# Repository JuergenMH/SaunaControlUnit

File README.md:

# SaunaControlUnit
Control unit for sauna oven. Ensures comfort and safety.
Cheap control units are good for regualation and some basic safetey functions.
This project is designed to add some comfort and safety topics
- Enhanced safety by control internal power lines and oven function
- Enhanced comfort: Acceess via WLAN
- Two relay banks to ensure the system in case of one relay fails

Folders:
Components: Datasheets and information hardware component related
Documents:  Planning Documents
SaunaPCB:   KiCAD folder for schematic and PCB design files
Simulation: Folder for LTSpice simulation fils
Firmware:   Planned for firmware files, currently empty

Sorry, some documents are available in German only ;-)

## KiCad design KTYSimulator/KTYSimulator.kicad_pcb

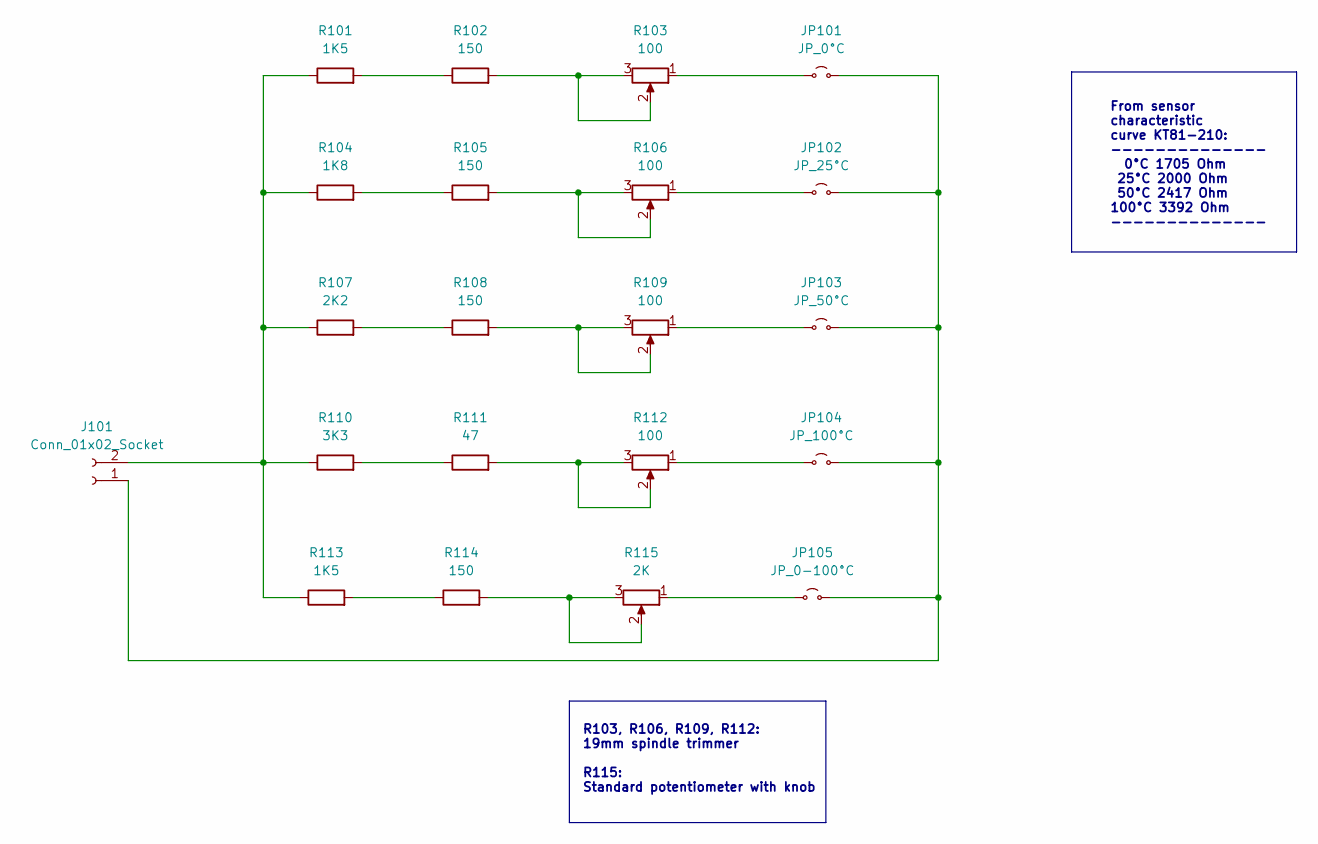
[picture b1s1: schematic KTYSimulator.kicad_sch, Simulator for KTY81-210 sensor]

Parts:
J101: Conn_01x02_Socket; PinHeader_1x02_P2.54mm_Vertical
JP101: JP_0°C; PinHeader_1x02_P2.54mm_Vertical
JP102: JP_25°C; PinHeader_1x02_P2.54mm_Vertical
JP103: JP_50°C; PinHeader_1x02_P2.54mm_Vertical
JP104: JP_100°C; PinHeader_1x02_P2.54mm_Vertical
JP105: JP_0-100°C; PinHeader_1x02_P2.54mm_Vertical
R101, R113: 1K5; R_Axial_DIN0207_L6.3mm_D2.5mm_P10.16mm_Horizontal
R102, R105, R108, R114: 150; R_Axial_DIN0207_L6.3mm_D2.5mm_P10.16mm_Horizontal
R103, R106, R109, R112: 100; Potentiometer_Bourns_3005_Horizontal
R104: 1K8; R_Axial_DIN0207_L6.3mm_D2.5mm_P10.16mm_Horizontal
R107: 2K2; R_Axial_DIN0207_L6.3mm_D2.5mm_P10.16mm_Horizontal
R110: 3K3; R_Axial_DIN0207_L6.3mm_D2.5mm_P10.16mm_Horizontal
R111: 47; R_Axial_DIN0207_L6.3mm_D2.5mm_P10.16mm_Horizontal
R115: 2K; Potentiometer_Alps_RK09Y11_Single_Horizontal

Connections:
unnamed: J101.1, JP101.2 (B), JP102.2 (B), JP103.2 (B), JP104.2 (B), JP105.2 (B)
unnamed: J101.2, R101.1, R104.1, R107.1, R110.1, R113.1
unnamed: JP101.1 (A), R103.1
unnamed: JP102.1 (A), R106.1
unnamed: JP103.1 (A), R109.1
unnamed: JP104.1 (A), R112.1
unnamed: JP105.1 (A), R115.1
unnamed: R101.2, R102.1
unnamed: R102.2, R103.2, R103.3
unnamed: R104.2, R105.1
unnamed: R105.2, R106.2, R106.3
unnamed: R107.2, R108.1
unnamed: R108.2, R109.2, R109.3
unnamed: R110.2, R111.1
unnamed: R111.2, R112.2, R112.3
unnamed: R113.2, R114.1
unnamed: R114.2, R115.2, R115.3

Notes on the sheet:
From sensor characteristic curve KT81-210: -------------- 0°C 1705 Ohm 25°C 2000 Ohm 50°C 2417 Ohm 100°C 3392 Ohm --------------
R103, R106, R109, R112: 19mm spindle trimmer R115: Standard potentiometer with knob

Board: 2 copper layers, 21 parts (0 on the bottom side), 17 nets, no tracks yet.

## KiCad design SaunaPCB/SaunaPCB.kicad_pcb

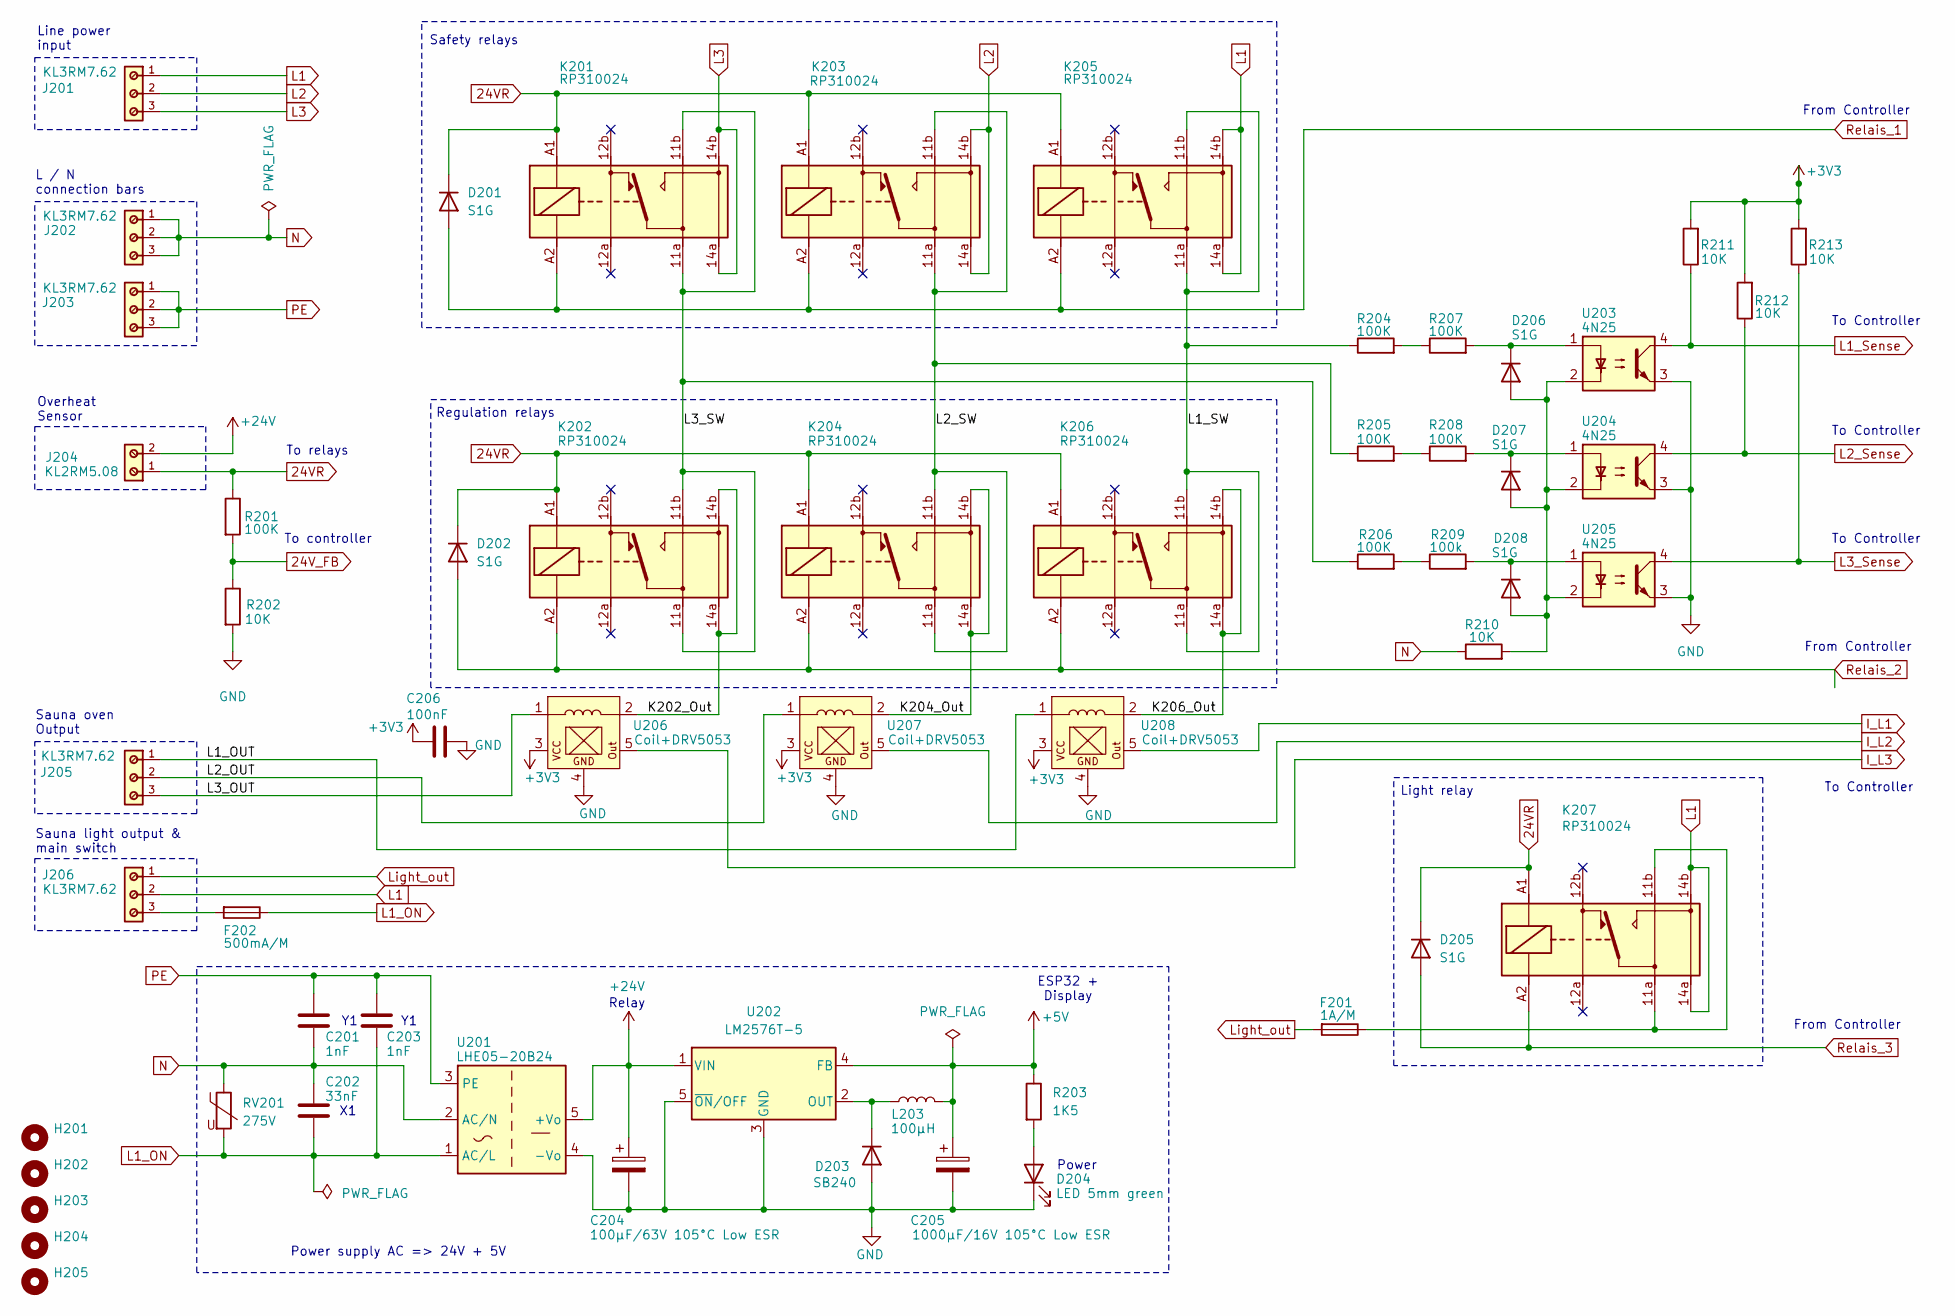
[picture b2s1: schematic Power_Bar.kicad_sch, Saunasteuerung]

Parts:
C201, C203: 1nF; C_Axial_L12.0mm_D6.5mm_P15.00mm_Horizontal
C202: 33nF; C_Axial_L12.0mm_D6.5mm_P15.00mm_Horizontal
C204: 100µF/63V 105°C Low ESR; CP_Radial_D10.0mm_P5.00mm
C205: 1000µF/16V 105°C Low ESR; CP_Radial_D10.0mm_P5.00mm
C206: 100nF; C_0805_2012Metric
D201, D202, D205, D206, D207, D208: S1G; D_SMA_Handsoldering
D203: SB240; D_A-405_P10.16mm_Horizontal
D204: LED 5mm green; B2B-ZR
F201: 1A/M; Fuseholder_Cylinder-5x20mm_Schurter_0031_8201_Horizontal_Op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
F202: 500mA/M; Fuseholder_Cylinder-5x20mm_Schurter_0031_8201_Horizontal_Op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
H201, H202, H203, H204, H205: MountingHole; MountingHole_3.2mm_M3_DIN965
J201, J202, J203, J205, J206: KL3RM7.62; Terminal_Block_3_RM7.62
J204: KL2RM5.08; Terminal_Block_2_RM5.08
K201, K202, K203, K204, K205, K206, K207: RP310024; Standard_Relay_double Pins
L203: 100µH; L_Radial_D7.5mm_P5.00mm_Fastron_07P
R201, R204, R205, R206, R207, R208: 100K; R_1206_3216Metric
R202, R210, R211, R212, R213: 10K; R_1206_3216Metric
R203: 1K5; R_1206_3216Metric
R209: 100k; R_1206_3216Metric
RV201: 275V; RV_Disc_D12mm_W4.2mm_P7.5mm
U201: LHE05-20B24
U202: LM2576T-5; TO-220-5_Vertical
U203, U204, U205: 4N25; DIP-4_W7.62mm
U206, U207, U208: Coil+DRV5053; Current_Coil_19X14_w_Hall

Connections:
24VR: D201.1 (K), D202.1 (K), D205.1 (K), J204.1, K201.A1, K202.A1, K203.A1, K204.A1, K205.A1, K206.A1, K207.A1, R201.1; also elsewhere on the board
24V_FB: R201.2, R202.1; also elsewhere on the board
+3V3: C206.1, R211.2, R212.2, R213.2, U206.3, U207.3, U208.3; also elsewhere on the board
+5V: C205.1, L203.2, R203.1, U202.4 (FB); also elsewhere on the board
+24V: C204.1, J204.2, U201.5 (+Vo), U202.1 (VIN)
/Power distribution part/K202_Out: K202.14a, K202.14b, U206.2
/Power distribution part/K204_Out: K204.14a, K204.14b, U207.2
/Power distribution part/K206_Out: K206.14a, K206.14b, U208.2
/Power distribution part/L1_OUT: J205.1, U208.1
/Power distribution part/L1_SW: K205.11a, K205.11b, K206.11a, K206.11b, R204.1
/Power distribution part/L2_OUT: J205.2, U207.1
/Power distribution part/L2_SW: K203.11a, K203.11b, K204.11a, K204.11b, R205.1
/Power distribution part/L3_OUT: J205.3, U206.1
/Power distribution part/L3_SW: K201.11a, K201.11b, K202.11a, K202.11b, R206.1
GND: C204.2, C205.2, C206.2, D203.2 (A), D204.1 (K), R202.2, U201.4 (-Vo), U202.3 (GND), U202.5 (~ON/OFF), U203.3, U204.3, U205.3, U206.4, U207.4, U208.4; also elsewhere on the board
I_L1: U208.5; also elsewhere on the board
I_L2: U207.5; also elsewhere on the board
I_L3: U206.5; also elsewhere on the board
L1: J201.1, J206.2, K205.14a, K205.14b, K207.14a, K207.14b
L1_ON: C202.2, C203.2, F202.1, RV201.2, U201.1 (AC/L)
L1_Sense: R211.1, U203.4; also elsewhere on the board
L2: J201.2, K203.14a, K203.14b
L2_Sense: R212.1, U204.4; also elsewhere on the board
L3: J201.3, K201.14a, K201.14b
L3_Sense: R213.1, U205.4; also elsewhere on the board
Light_out: F201.2, J206.1
N: C201.2, C202.1, J202.1, J202.2, J202.3, R210.1, RV201.1, U201.2 (AC/N)
unnamed: D203.1 (K), L203.1, U202.2 (OUT)
unnamed: D204.2 (A), R203.2
unnamed: D206.2 (A), D207.2 (A), D208.2 (A), R210.2, U203.2, U204.2, U205.2
unnamed: D206.1 (K), R207.2, U203.1
unnamed: D207.1 (K), R208.2, U204.1
unnamed: D208.1 (K), R209.2, U205.1
unnamed: F201.1, K207.11a, K207.11b
unnamed: F202.2, J206.3
unnamed: R204.2, R207.1
unnamed: R205.2, R208.1
unnamed: R206.2, R209.1
PE: C201.1, C203.1, J203.1, J203.2, J203.3, U201.3 (PE)
Relais_1: D201.2 (A), K201.A2, K203.A2, K205.A2; also elsewhere on the board
Relais_2: D202.2 (A), K202.A2, K204.A2, K206.A2; also elsewhere on the board
Relais_3: D205.2 (A), K207.A2; also elsewhere on the board

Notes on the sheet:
From Controller
Power supply AC => 24V + 5V
Regulation relays
L / N connection bars
To Controller
Light relay
Overheat Sensor
Sauna oven Output
To relays
To controller
Safety relays
Line power input
Sauna light output & main switch
Power
ESP32 + Display
Relay

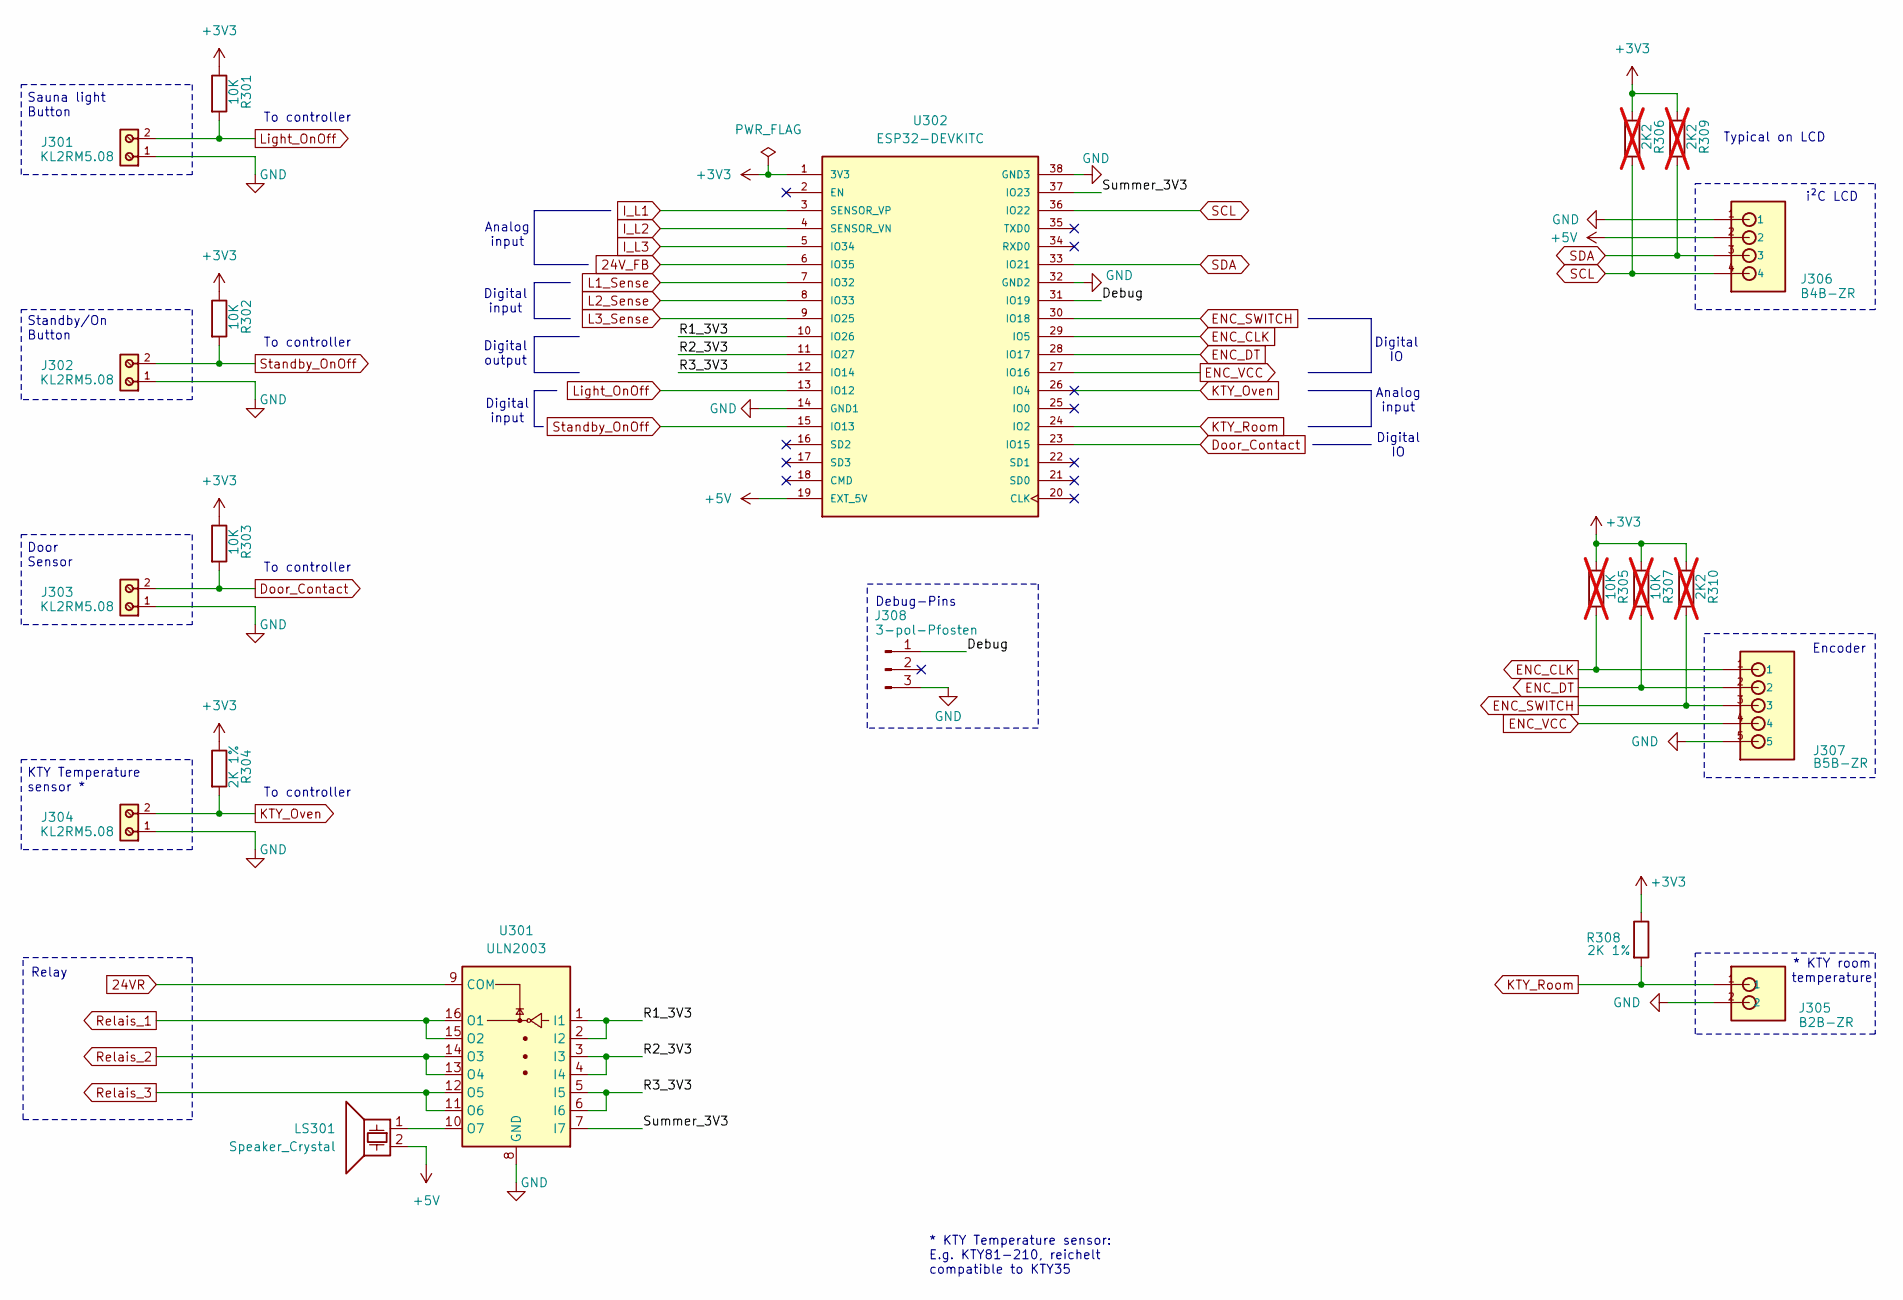
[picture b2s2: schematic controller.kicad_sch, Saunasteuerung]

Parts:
J301, J302, J303, J304: KL2RM5.08; Terminal_Block_2_RM5.08
J305: B2B-ZR
J306: B4B-ZR
J307: B5B-ZR
J308: 3-pol-Pfosten; PinHeader_1x03_P1.00mm_Vertical
LS301: Speaker_Crystal; Buzzer_TDK_PS1240P02BT_D12.2mm_H6.5mm
R301, R302, R303: 10K; R_1206_3216Metric
R304, R308: 2K 1%; R_1206_3216Metric
R305, R307: 10K; R_1206_3216Metric; not fitted
R306, R309, R310: 2K2; R_1206_3216Metric; not fitted
U301: ULN2003; DIP-16_W7.62mm
U302: ESP32-DEVKITC; ESP32_DevKit_V4; PARTREV N/A

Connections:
24VR: U301.9 (COM); also elsewhere on the board
24V_FB: U302.6 (IO35); also elsewhere on the board
+3V3: R301.1, R302.1, R303.1, R304.1, R305.1, R306.1, R307.1, R308.1, R309.1, R310.1, U302.1 (3V3); also elsewhere on the board
+5V: J306.2, LS301.2, U302.19 (EXT_5V); also elsewhere on the board
/Controller part/Debug: J308.1, U302.31 (IO19)
/Controller part/R1_3V3: U301.1 (I1), U301.2 (I2), U302.10 (IO26)
/Controller part/R2_3V3: U301.3 (I3), U301.4 (I4), U302.11 (IO27)
/Controller part/R3_3V3: U301.5 (I5), U301.6 (I6), U302.12 (IO14)
/Controller part/Summer_3V3: U301.7 (I7), U302.37 (IO23)
Door_Contact: J303.2, R303.2, U302.23 (IO15)
ENC_CLK: J307.1, R305.2, U302.29 (IO5)
ENC_DT: J307.2, R307.2, U302.28 (IO17)
ENC_SWITCH: J307.3, R310.2, U302.30 (IO18)
ENC_VCC: J307.4, U302.27 (IO16)
GND: J301.1, J302.1, J303.1, J304.1, J305.2, J306.1, J307.5, J308.3, U301.8 (GND), U302.14 (GND1), U302.32 (GND2), U302.38 (GND3); also elsewhere on the board
I_L1: U302.3 (SENSOR_VP); also elsewhere on the board
I_L2: U302.4 (SENSOR_VN); also elsewhere on the board
I_L3: U302.5 (IO34); also elsewhere on the board
KTY_Oven: J304.2, R304.2, U302.26 (IO4)
KTY_Room: J305.1, R308.2, U302.24 (IO2)
L1_Sense: U302.7 (IO32); also elsewhere on the board
L2_Sense: U302.8 (IO33); also elsewhere on the board
L3_Sense: U302.9 (IO25); also elsewhere on the board
Light_OnOff: J301.2, R301.2, U302.13 (IO12)
unnamed: LS301.1, U301.10 (O7)
Relais_1: U301.15 (O2), U301.16 (O1); also elsewhere on the board
Relais_2: U301.13 (O4), U301.14 (O3); also elsewhere on the board
Relais_3: U301.11 (O6), U301.12 (O5); also elsewhere on the board
SCL: J306.4, R306.2, U302.36 (IO22)
SDA: J306.3, R309.2, U302.33 (IO21)
Standby_OnOff: J302.2, R302.2, U302.15 (IO13)

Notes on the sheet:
Typical on LCD
i²C LCD
Digital input
* KTY Temperature sensor: E.g. KTY81-210, reichelt compatible to KTY35
Analog input
Standby/On Button
Debug-Pins
To controller
Encoder
Digital output
Sauna light Button
Digital IO
Relay
KTY Temperature sensor *
Door Sensor
* KTY room temperature

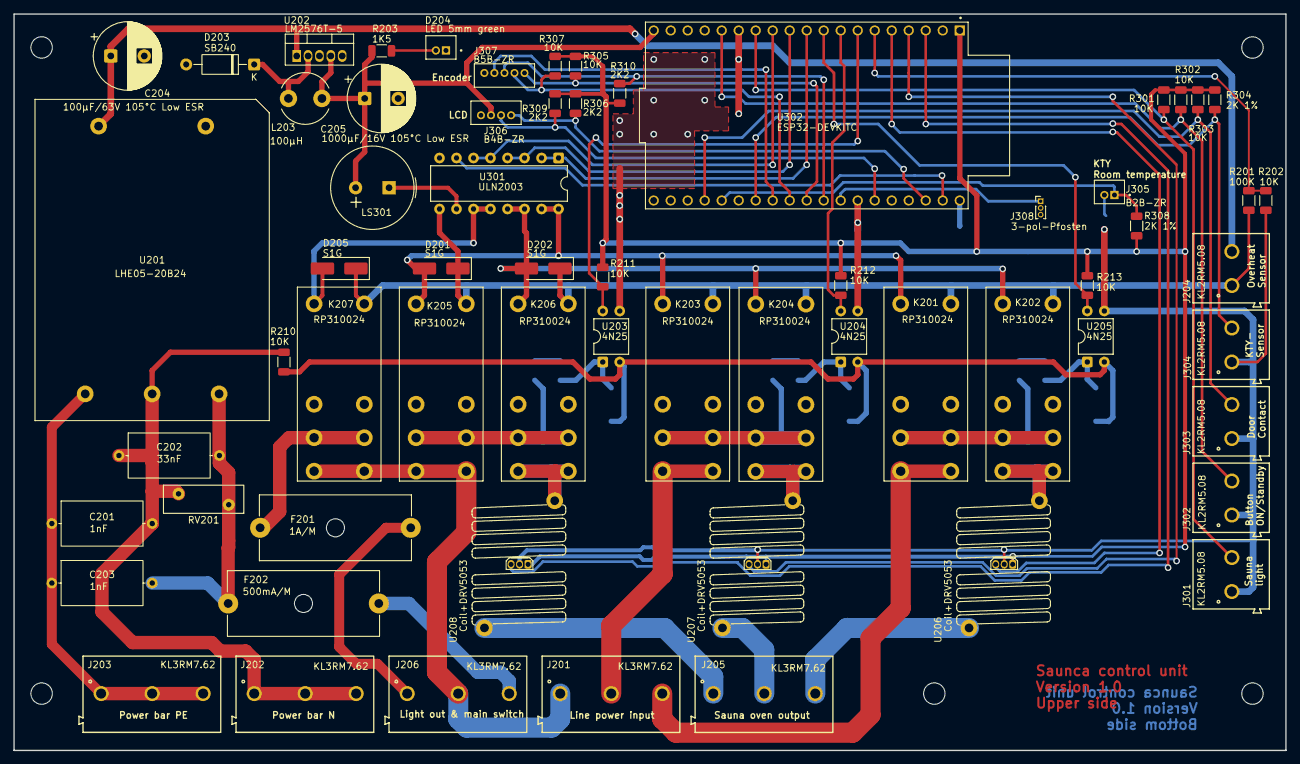
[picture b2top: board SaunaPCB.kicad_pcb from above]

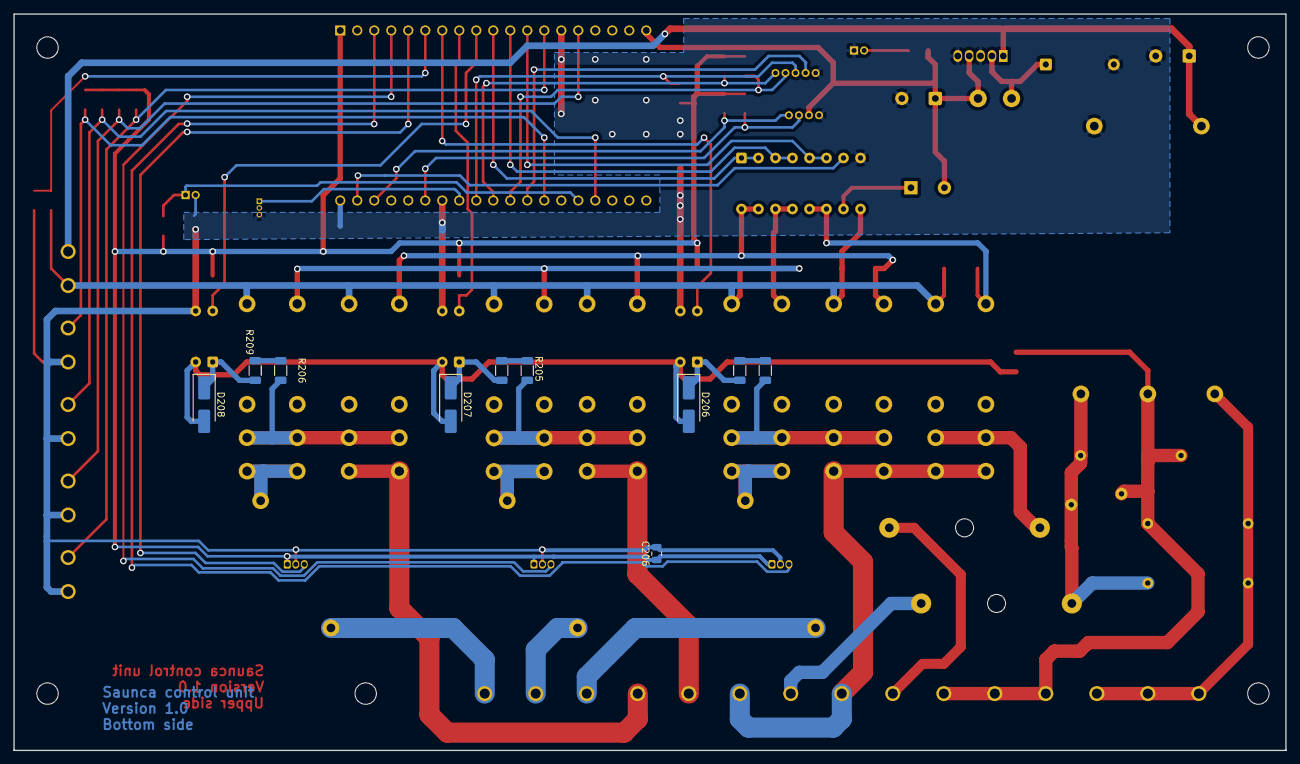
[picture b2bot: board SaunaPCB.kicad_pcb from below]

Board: 2 copper layers, 190.0 x 110.0 mm, 78 parts (10 on the bottom side), 59 nets.

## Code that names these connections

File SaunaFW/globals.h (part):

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#define I2C_SDA             21      // default SDA for ESP32
#define I2C_SCL             22      // ditto SCL

#define ENC_CLK             5       // Signal A interrupt
#define ENC_DT              17      // Signal B to interrupt
#define ENC_SW              18      // Signal button, to interrupt
#define ENC_VCC             16      // control vcc of the encoder

#define RELAY_1             26      // 3.3V signal for relay group #1 (safety)
#define RELAY_2             27      // ditto relay group #2 (regulation)
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#define INP_LIGHT           12      // light on/off button on GPIO12
#define INP_MODE            13      // mode: on, standby ....

#define DEBUG_1             19      // Debug pin #1

#define KTY_35              4       // oven sensor = KTY_35
#define KTY_81              2       // room sensor = KTY_81
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
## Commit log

2026-01-24 Update README with features and safety enhancements
    Added features and benefits of the sauna control unit.
2026-01-24 First commit: basic file and folder set added.
2026-01-24 Firmware folder (empty) added; Ready information update.
2026-01-25 Data home brew current sensor added
2026-01-25 Working on schematic and PCB -AC/DC and DC/DC converters with correct symbol and footprint now - rough placement of the power parts
2026-01-26 Work on documnets and net classes
2026-01-27 PCB Planning.docx added
2026-01-27 Temp file for 70µm added tool not running on my lg :-(
2026-01-30 Rework trace width calculation Distances (legal requirements) added
2026-01-30 Working on PCB placment optimisation Trace width and distance
2026-01-30 Working on planning document (still legal topics)
2026-01-31 Still working on placement and routing
2026-01-31 Relay power supply changed
2026-02-01 Working on schematic: - Own ESP32 Devkit V4 device used. - ESP32 connections added (all signals from page on connected)
    - Next steps: Connection to LCD, Relay driver, Encoder Interface and standby LED
2026-02-01 Minor changes on port usage
2026-02-03 5V regulator changed
2026-02-04 some step files added
2026-02-05 Hall sensors for current measurement added
2026-02-05 backup file removed
2026-02-06 Datasheet hall sensors added, folder structure changed
2026-02-06 Hall effect sensor type changed to DRV5053 .gitignore added: ignore .zip files in KiCAD backup folder
2026-02-06 First routing almost finished Connector to LCD and encoder to be added!
2026-02-06 Connector to LCD and decoder added
2026-02-07 Usage ULN changed Top silkscreen PCB almost ready Values Diodes changed all 1N4004 => SG1 Relay diodes changed from NB to used (for security reasons; Diode in ULN may be not powerful enough)
2026-02-07 Firmware coding started. LCD and encoder running
    todos
    - encoder change from polling to interrupt usage
    - switch input connected to interrupt input
2026-02-08 ^MOV and Fuse added
2026-02-08 Moved to port planning excel-sheet
2026-02-08 Power LED changed to JST connector KTY room added
2026-02-08 Update port planning Documents/Manual_K2_(simple_control_unit).pdf
    - VCC encoder from controller now
    - KTY room added
    - buzzer added
2026-02-08 Standard encoder library replaced by ESP specific library. Full interrupt driven. New module to bundle all encoder specific integration
    Test code for new libary in loop.
2026-02-08 Working on the SW:
    - Hardware timer 1ms running
    - Scheduler 1/5 ms running
    - Relay and Application module with stubs (no function yet)
2026-02-08 Coding of relay FSM finished. Code can be compiled but is not tested!
2026-02-09 Second FW folder removed (not necessary anymore)
2026-02-09 Plot folder with plot files added.
2026-02-09 KTY calculation sheet added (made with Copilot 365)
2026-02-09 Module for KTY added direct from KI, not adjusted at current structure.
2026-02-10 Unknown changes from BEKO laptop
2026-02-10 autosafe file removed
2026-02-11 Home brew sensor: Coil and hall sensor combined to one unit to avoid overlap errors on DRC DRC errors removed; 2 warnings left => both acceptable.
2026-02-11 MyIODrive with input debouncer and edge generation added. Code can be compiled but is not tested.
    KTY module can also be compiled but is not used and not tested.
2026-02-12 Backlight signal removed two debug pins added remarks regarding KTY added
2026-02-12 Input debouncer and edge generator are working now. Next step: connect light button with relay 3 FSM to test the FSM.
2026-02-13 Working on relay function. Code can not be compiled in this version.
2026-02-13 - Relay module reworked. Now ready & tested. - Light handler to Task51 added to handle light button in the background. - Error in SW timer removed - Run time task 51 performed (less 3µs!)
    Functions described above are working fine and as expected
2026-02-14 Temperature functions implemented:
    - KTY module implemented in scheduling
    - Two channels to be calculated
    - change flags are generated
    Code can be compiled (run time about 100µs), but is not tested yet!
2026-02-14 Working on KTY module. => Module gives temperature values, but not plausible
    maybe a sensor issue, to be checked.
    Test code for KTY moved to text file.
2026-02-14 Start working on GUI
2026-02-15 Module renaming: Now all modules starts with My...
2026-02-15 Inter mediate check in: working on GUI not finished, lCD is pretty slow, new concept to be implemented!
2026-02-22 Room KTY moved to IO0 (prior buzzer) Buzzer moved to IO23 (prior Debung_2) Debug_2 removed
    Reason IO0 does not work properly as ADC input.
    Pretty low input impediance...
2026-03-19 Document folder update: - chaned IO Port_Usage_Planning.xls - new information regarding KTY81 - textfile with usefuls links
2026-03-22 Software changed from cooperative multi tasking to preemptive multi tasking based on the ESP32 FreeRTOS
    The following tasks are coded and running and roughly tested as OK:
    -------------------------------------------------------------------
    - Relay_x tasks are running, tested, OK
    - IODrive task is running; , tested, OK
    - High watermark (=stack) check task is running, tested OK
    These tasks are not OK and must be debugged / fixed:
2026-03-22 Remarks to port usage added
2026-03-22 Simulator circuit to give different temperatures. Useful for test of KTY measurement and debug the regulation algorithm.
